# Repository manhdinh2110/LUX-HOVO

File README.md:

# LUX-HOVO
An exclusive archive by the LUXHOVO R&amp;D team, featuring project workflows, intricate design schematics, and essential development source code.

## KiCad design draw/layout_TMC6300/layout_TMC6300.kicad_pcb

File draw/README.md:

# PCB Develop Environment
KICAD 8.0

# MECHANICAL & 3D
Rhino 7

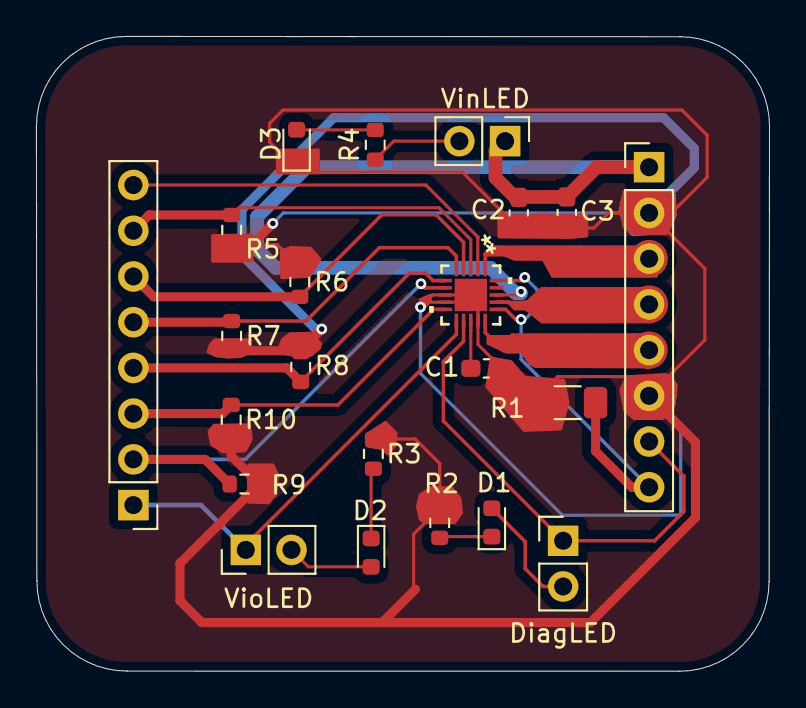
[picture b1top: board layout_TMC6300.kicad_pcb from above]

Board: 2 copper layers, 40.7 x 35.3 mm, 22 parts (0 on the bottom side), 22 nets.

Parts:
C1, C2: 0.1uF; C_0603_1608Metric_Pad1.08x0.95mm_HandSolder
C3: 10uF; C_0603_1608Metric_Pad1.08x0.95mm_HandSolder
D1: RED; LED_0603_1608Metric
D2: BLUE; LED_0603_1608Metric
D3: GREEN; LED_0603_1608Metric
DiagLED: DiagLED; PinHeader_1x02_P2.54mm_Vertical
J1: INPUT; PinHeader_1x08_P2.54mm_Vertical
J2: OUTPUT; PinHeader_1x08_P2.54mm_Vertical
R1: 0.12; R_1206_3216Metric_Pad1.30x1.75mm_HandSolder
R2: 330; R_0603_1608Metric
R3: 2.2k; R_0603_1608Metric
R4: 1k; R_0603_1608Metric
R5, R6, R7, R8, R9, R10: 100k; R_0603_1608Metric
U2: TMC6300-LA-T; 21-100586_K2033&plus_1C_ADI
VinLED: VinLED; PinHeader_1x02_P2.54mm_Vertical
VioLED: VioLED; PinHeader_1x02_P2.54mm_Vertical

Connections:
/DiagLedConn: D1.2 (A), DiagLED.2
/VinLedConn: R4.1, VinLED.2
/VioLedConn: D2.2 (A), VioLED.2
DIAG: DiagLED.1, J2.7, U2.12 (DIAG)
GND: C1.2, C2.2, C3.2, D3.1 (K), J2.2, J2.6, R1.2, R2.2, R3.2, R5.2, R6.2, R7.2, R8.2, R9.2, R10.2, U2.8 (GND), U2.9 (GND), U2.14 (GND), U2.21 (GND)
unnamed: D1.1 (K), R2.1
unnamed: D2.1 (K), R3.1
unnamed: D3.2 (A), R4.2
unnamed: C1.1, U2.13 (1.8VOUT)
SENSE: J2.8, R1.1, U2.16 (BRUV), U2.20 (BRW)
U: J2.5, U2.15 (U)
UH: J1.7, R5.1, U2.3 (UH)
UL: J1.4, R8.1, U2.6 (UL)
V: J2.4, U2.17 (V)
VCP: J1.8, U2.2 (VCP)
VH: J1.6, R6.1, U2.4 (VH)
VIN: C2.1, C3.1, J2.1, U2.18 (VS), VinLED.1
VIO: J1.1, U2.11 (VIO/NSTDBY), VioLED.1
VL: J1.3, R10.1, U2.10 (VL)
W: J2.3, U2.1 (W)
WH: J1.5, R7.1, U2.5 (WH)
WL: J1.2, R9.1, U2.7 (WL)

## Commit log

2024-11-12 feat: template stm32 kielC
2024-11-12 feat: template STM32 in KeilC
2024-11-16 Create Arduino
2024-11-16 add file driver
2024-11-19 feat: template screen
2024-11-19 feat: page clock
